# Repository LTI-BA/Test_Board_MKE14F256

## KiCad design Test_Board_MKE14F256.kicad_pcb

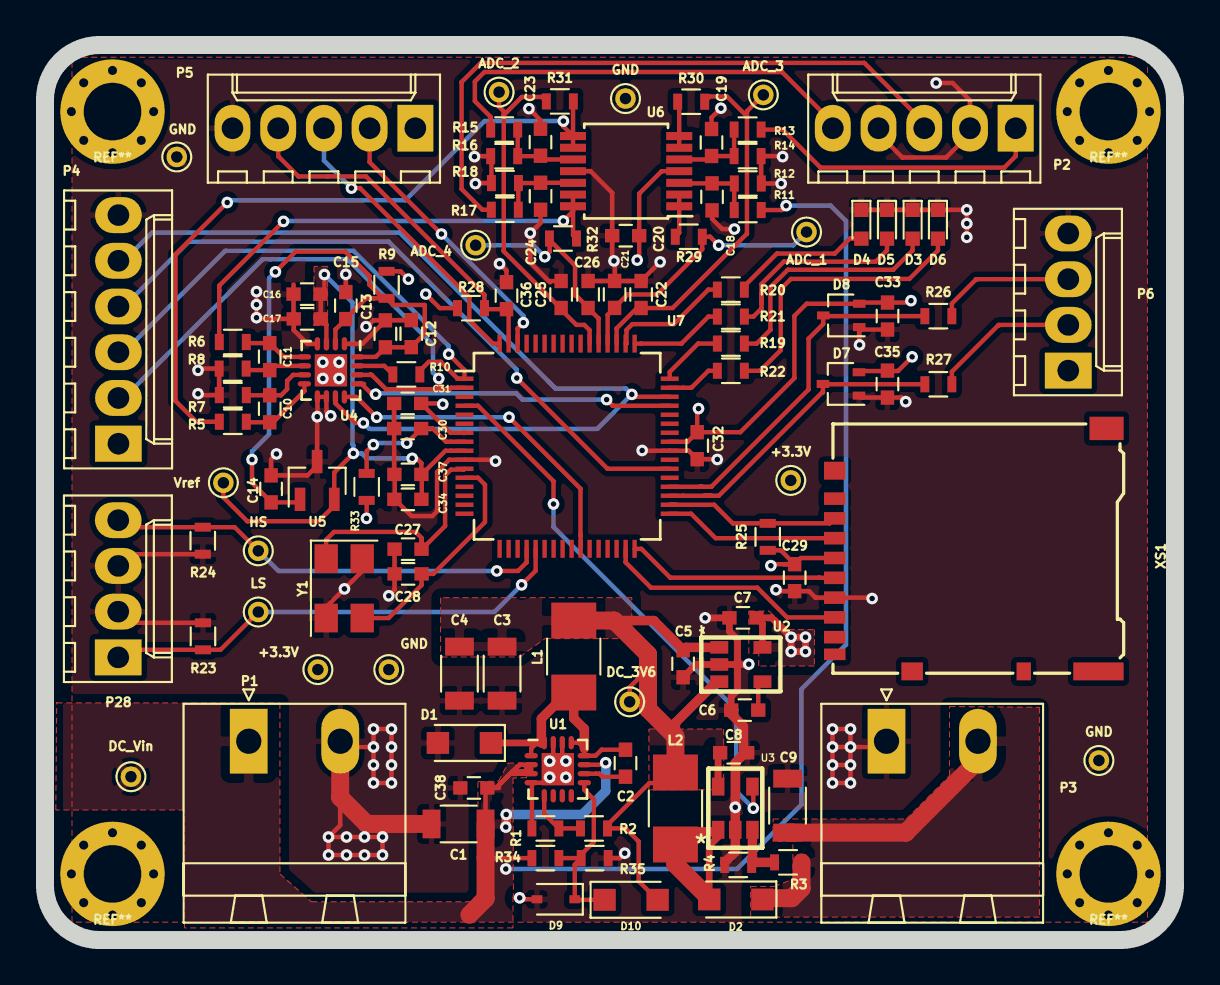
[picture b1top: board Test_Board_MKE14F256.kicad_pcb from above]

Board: 4 copper layers, 62.8 x 49.7 mm, 116 parts (0 on the bottom side), 65 nets.

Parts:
+3.3V, +3.3V#2: CONN_01X01; PINTST
ADC_1, ADC_2, ADC_3, ADC_4: CONN_01X01; PINTST
C1, C9: 10u; C_1206
C2, C13, C17, C20, C29, C30, C31, C32, C33, C35, C36, C38: 100n; C_0603
C3, C4: 22u; C_1206
C5, C7, C12, C15: 1u; C_0603
C6, C37: 10n; C_0603
C8: 2.2u; C_0603
C10, C11, C21, C22, C25, C26: 470p; C_0603
C14: 470n; C_0603
C16: 10u; C_0603
C18, C19, C23, C24: 180p; C_0603
C27, C28: 18p; C_0603
C34: 1n; C_0603
D1: D_Schottky_Small; D_SOD-123
D2: Sch.; D_SOD-123
D3: red; LED_0603
D4: yel; LED_0603
D5: grn; LED_0603
D6: ble; LED_0603
D7, D8: BAT54SW; SOT-323_SC-70
D9: D_Zener_Small; D_SOD-323
D10: D_Schottky; D_SOD-123
DC_3V6: CONN_01X01; PINTST
DC_Vin: CONN_01X01; PINTST
GND: CONN_01X01; PINTST
GND#2, GND#3, GND#4: CONN_01X01; PINTST
HS: CONN_01X01; PINTST
L1: 4.7u; R_1210_HandSoldering
L2: 10u; R_1210_HandSoldering
LS: CONN_01X01; PINTST
P1, P3: CONN_01X02; PhoenixContact_MSTBA-G_02x5.08mm_Angled
P2: CONN_01X04; Molex_KK-6410-05_05x2.54mm_Straight
P4: CONN_01X06; Molex_KK-6410-06_06x2.54mm_Straight
P5: CONN_01X05; Molex_KK-6410-05_05x2.54mm_Straight
P6, P28: CONN_01X04; Molex_KK-6410-04_04x2.54mm_Straight
R1, R12, R14, R16, R18, R23, R24, R28, R35: 10k; R_0603
R2, R34: 30k; R_0603
R3: 91k; R_0603
R4: 8.2k; R_0603
R5, R6, R7, R8, R9, R29, R30, R31, R32, R33: 5; R_0603
R10: 47; R_0603
R11, R13, R15, R17: 110k; R_0603
R19, R20, R21, R22: 470; R_0603
R25: 47k; R_0603
R26, R27: 22; R_0603
U1: TS3004; QFN-16-1EP_3x3mm_Pitch0.5mm
U2: NCP700B; TSOP-5
U3: MIC2288; TSOP-5
U4: ADS79XX; QFN-16-1EP_3x3mm_Pitch0.5mm
U5: REF3030; SOT-23
U6: TSV524A; TSSOP-14_4.4x5mm_Pitch0.65mm
U7: MKE14F256_v.1.2; LQFP-64_10x10mm_Pitch0.5mm
Vref: CONN_01X01; PINTST
XS1: SD_ebay-uSD-push/push_SMD; HIROSE-MICROSD-DM3AT-SF
Y1: ABMM2-8.000MHZ-E2-T; Crystal_SMD_5032-4pin_5.0x3.2mm

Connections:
+3V3: +3.3V.1, +3.3V#2.1, C7.1, C20.1, C29.2, C31.2, C32.2, C33.1, C35.1, D7.2, D8.2, P4.1, P5.1, P6.1, R9.2, R25.1, R28.2, R33.1, U2.5, U6.4, U7.7, U7.41, XS1.4
+15V: C9.2, D2.1, P3.2, R3.1
ADC_1: ADC_1.1, C21.1, R29.1, U7.52
ADC_2: ADC_2.1, C25.1, R31.1, U7.54
ADC_3: ADC_3.1, C22.1, R30.1, U7.51
ADC_4: ADC_4.1, C26.1, R32.1, U7.53
ADC_PDEN: U4.12, U7.26
ADC_SPI1_CS0: U4.13, U7.45
ADC_SPI1_CS1: P4.4, U7.38
ADC_SPI1_MOSI_ADC_CH_SEL: P4.5, U4.11, U7.46
ADC_SPI1_SCLK: P4.2, U4.14, U7.2
ADC_SPI1_SDO: P4.3, R10.1, U7.1
Boost_Enable: U3.4, U7.4
DC_3V6: C3.1, C4.1, C5.1, C8.1, D10.2, DC_3V6.1, L1.2, L2.1, R2.1, U2.1, U2.3, U3.5
DC_Vin: C1.2, C38.2, DC_Vin.1, P1.1, R11.1, R34.2, U1.2, U1.3, U1.11
GND: C1.1, C3.2, C4.2, C5.2, C6.2, C7.2, C8.2, C9.1, C12.2, C13.2, C14.2, C15.2, C16.2, C17.2, C18.2, C19.2, C20.2, C21.2, C22.2, C23.2, C24.2, C25.2, C26.2, C27.2, C28.2, C29.1, C30.1, C31.1, C32.1, C33.2, C34.1, C35.2, C36.2, C37.1, C38.1, D1.2, D3.1, D4.1, D5.1, D6.1, D7.1, D8.1, D9.2, GND.1, GND#2.1, GND#3.1, GND#4.1, P1.2, P2.2, P2.4, P3.1, P4.6, P5.5, P6.4, P28.2, P28.3, R1.2, R4.2, R7.1, R8.1, R12.2, R14.2, R16.2, R18.2, R23.2, R24.2, R35.1, U1.4, U1.14, U1.15, U2.2, U3.2, U4.1, U4.4, U4.9, U4.10, U5.3, U6.11, U7.10, U7.40, XS1.6, Y1.2, Y1.4
unnamed: C2.1, U1.10
unnamed: C2.2, D1.1, L1.1, U1.1, U1.12, U1.13, U1.16
unnamed: C6.1, U2.4
unnamed: C10.1, R5.2, U4.8
unnamed: C10.2, R7.2, U4.7
unnamed: C11.1, R8.2, U4.6
unnamed: C11.2, R6.2, U4.5
unnamed: C12.1, C13.1, C14.1, C15.1, R9.1, U4.2, U4.16, U5.1
unnamed: C18.1, R11.2, R12.1, U6.3
unnamed: C19.1, R13.2, R14.1, U6.5
unnamed: C23.1, R15.2, R16.1, U6.10
unnamed: C24.1, R17.2, R18.1, U6.12
unnamed: C27.1, U7.11, Y1.1
unnamed: C28.1, U7.12, Y1.3
unnamed: C30.2, R33.2, U7.8
unnamed: D2.2, L2.2, U3.1
unnamed: D3.2, R19.2
unnamed: D4.2, R20.2
unnamed: D5.2, R21.2
unnamed: D6.2, R22.2
unnamed: D9.1, D10.1, R34.1, R35.2, U1.9
unnamed: P6.2, R27.2
unnamed: P6.3, R26.2
unnamed: R1.1, R2.2, U1.5
unnamed: R3.2, R4.1, U3.3
unnamed: R10.2, U4.15
unnamed: R29.2, U6.1, U6.2
unnamed: R30.2, U6.6, U6.7
OpAmp_Out2: R5.1, R31.2, U6.8, U6.9
OpAmp_Out4: R6.1, R32.2, U6.13, U6.14
PWM_HS: HS.1, P28.4, R24.1, U7.20
PWM_LS: LS.1, P28.1, R23.1, U7.21
SWD_CLK: P5.2, U7.62
SWD_DIO_TGTMCU: P5.3, U7.64
SWD_RESET: C36.1, P5.4, R28.1, U7.63
UART1_RX: D8.3, R26.1, U7.36
UART1_TX: D7.3, R27.1, U7.35
V_in_2: P2.5, R15.1
V_in_3: P2.1, R13.1
V_in_4: P2.3, R17.1
Vref: C16.1, C17.1, C34.2, C37.2, U4.3, U5.2, U7.9, Vref.1
led_blu: R22.1, U7.47
led_grn: R21.1, U7.49
led_red: R19.1, U7.48
led_yel: R20.1, U7.50
uSD_SPI0_CS0: R25.2, U7.34, XS1.2
uSD_SPI0_DI: U7.33, XS1.3
uSD_SPI0_DO: U7.31, XS1.7
uSD_SPI0_SCLK: U7.32, XS1.5

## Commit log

2017-03-03 Test_Board_MKE14F256
2017-03-06 v1.0
2017-03-10 Stand 10.03
2017-03-18 schematics ==> Check (exept BW) Layout started
2017-04-05 changed usd slot
2017-04-05 All parts in places (exept :Leds)
2017-04-06 Started with tracking
2017-04-13 added missing parts (SPI conn / Boost Conn/ drills..)
2017-04-13 still the regulators & Planes fill
2017-04-15 routed the Buck & LDO ==> Still Boost
2017-04-15 connected Boost. Still inner layers
2017-04-15 Fixed some DRC errors
2017-04-17 Complete... Still some things to check
2017-04-18 corrected some mistakes listed in the email
